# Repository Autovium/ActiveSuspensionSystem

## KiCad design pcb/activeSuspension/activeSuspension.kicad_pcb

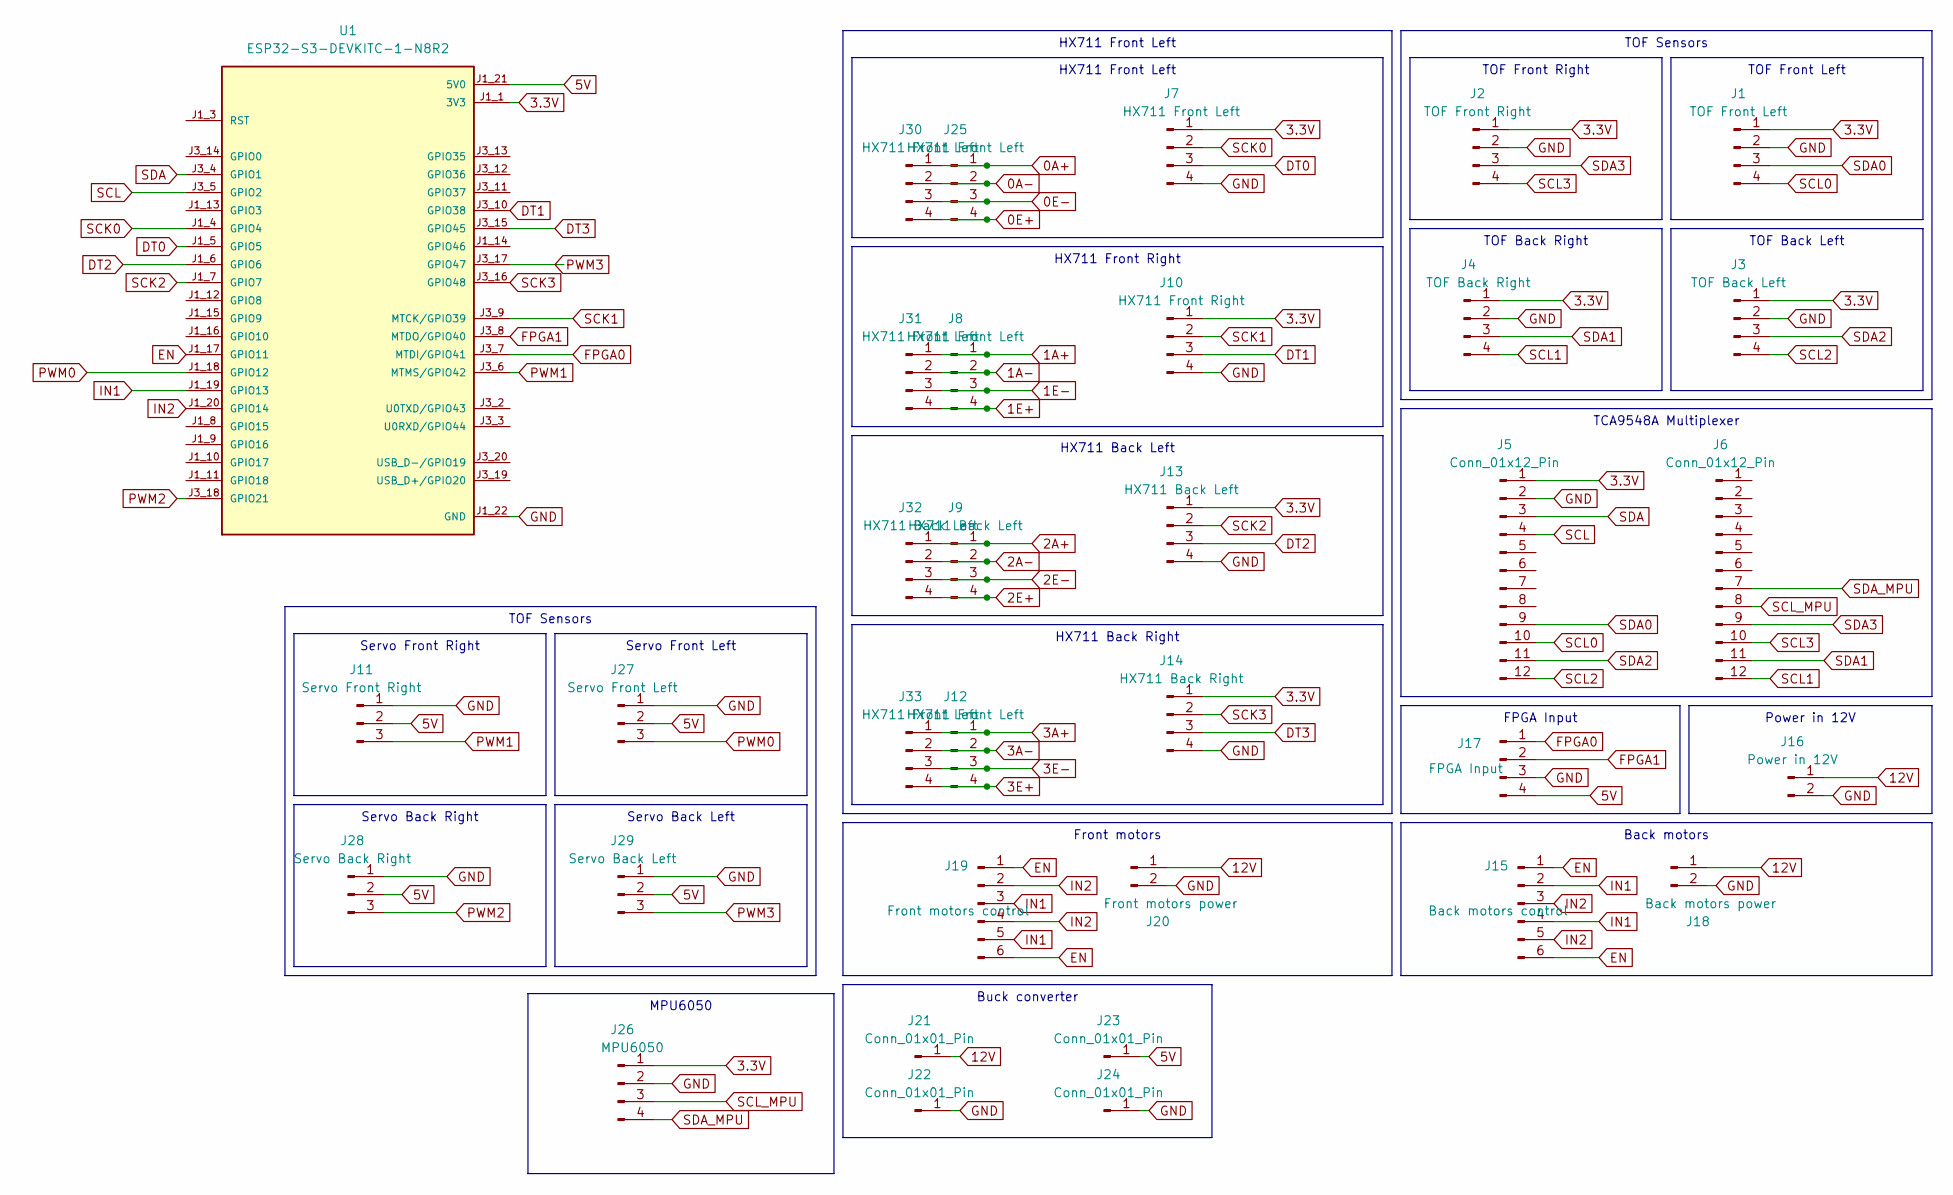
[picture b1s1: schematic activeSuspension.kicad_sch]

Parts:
J1: TOF Front Left; PinHeader_1x04_P2.54mm_Vertical
J2: TOF Front Right; PinHeader_1x04_P2.54mm_Vertical
J3: TOF Back Left; PinHeader_1x04_P2.54mm_Vertical
J4: TOF Back Right; PinHeader_1x04_P2.54mm_Vertical
J5, J6: Conn_01x12_Pin; PinHeader_1x12_P2.54mm_Vertical
J7, J8, J12, J25, J30, J31, J33: HX711 Front Left; PinHeader_1x04_P2.54mm_Vertical
J9, J13, J32: HX711 Back Left; PinHeader_1x04_P2.54mm_Vertical
J10: HX711 Front Right; PinHeader_1x04_P2.54mm_Vertical
J11: Servo Front Right; PinHeader_1x03_P2.54mm_Vertical
J14: HX711 Back Right; PinHeader_1x04_P2.54mm_Vertical
J15: Back motors control; PinHeader_1x06_P2.54mm_Vertical
J16: Power in 12V; PinHeader_1x02_P2.54mm_Vertical
J17: FPGA Input; PinHeader_1x04_P2.54mm_Vertical
J18: Back motors power; TerminalBlock_MetzConnect_Type101_RT01602HBWC_1x02_P5.08mm_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
J19: Front motors control; PinHeader_1x06_P2.54mm_Vertical
J20: Front motors power; TerminalBlock_MetzConnect_Type101_RT01602HBWC_1x02_P5.08mm_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
J21, J22, J23, J24: Conn_01x01_Pin; PinHeader_1x01_P2.54mm_Vertical
J26: MPU6050; PinHeader_1x04_P2.54mm_Vertical
J27: Servo Front Left; PinHeader_1x03_P2.54mm_Vertical
J28: Servo Back Right; PinHeader_1x03_P2.54mm_Vertical
J29: Servo Back Left; PinHeader_1x03_P2.54mm_Vertical
U1: ESP32-S3-DEVKITC-1-N8R2; XCVR_ESP32-S3-DEVKITC-1-N8R2; PARTREV V1

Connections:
0A+: J25.1, J30.1
0A-: J25.2, J30.2
0E+: J25.4, J30.4
0E-: J25.3, J30.3
1A+: J8.1, J31.1
1A-: J8.2, J31.2
1E+: J8.4, J31.4
1E-: J8.3, J31.3
2A+: J9.1, J32.1
2A-: J9.2, J32.2
2E+: J9.4, J32.4
2E-: J9.3, J32.3
3.3V: J1.1, J2.1, J3.1, J4.1, J5.1, J7.1, J10.1, J13.1, J14.1, J26.1, U1.J1_1 (3V3), U1.J1_2 (3V3)
3A+: J12.1, J33.1
3A-: J12.2, J33.2
3E+: J12.4, J33.4
3E-: J12.3, J33.3
5V: J11.2, J17.4, J23.1, J27.2, J28.2, J29.2, U1.J1_21 (5V0)
12V: J16.1, J18.1, J20.1, J21.1
DT0: J7.3, U1.J1_5 (GPIO5)
DT1: J10.3, U1.J3_10 (GPIO38)
DT2: J13.3, U1.J1_6 (GPIO6)
DT3: J14.3, U1.J3_13 (GPIO35), U1.J3_15 (GPIO45)
EN: J15.1, J15.6, J19.1, J19.6, U1.J1_17 (GPIO11)
FPGA0: J17.1, U1.J3_7 (MTDI/GPIO41)
FPGA1: J17.2, U1.J3_8 (MTDO/GPIO40)
GND: J1.2, J2.2, J3.2, J4.2, J5.2, J7.4, J10.4, J11.1, J13.4, J14.4, J16.2, J17.3, J18.2, J20.2, J22.1, J24.1, J26.2, J27.1, J28.1, J29.1, U1.J1_22 (GND), U1.J3_1 (GND), U1.J3_21 (GND), U1.J3_22 (GND)
IN1: J15.2, J15.4, J19.3, J19.5, U1.J1_19 (GPIO13)
IN2: J15.3, J15.5, J19.2, J19.4, U1.J1_20 (GPIO14)
PWM0: J27.3, U1.J1_18 (GPIO12)
PWM1: J11.3, U1.J3_6 (MTMS/GPIO42)
PWM2: J28.3, U1.J3_18 (GPIO21)
PWM3: J29.3, U1.J3_17 (GPIO47)
SCK0: J7.2, U1.J1_4 (GPIO4)
SCK1: J10.2, U1.J3_9 (MTCK/GPIO39)
SCK2: J13.2, U1.J1_7 (GPIO7)
SCK3: J14.2, U1.J3_12 (GPIO36), U1.J3_16 (GPIO48)
SCL: J5.4, U1.J3_5 (GPIO2)
SCL0: J1.4, J5.10
SCL1: J4.4, J6.12
SCL2: J3.4, J5.12
SCL3: J2.4, J6.10
SCL_MPU: J6.8, J26.3
SDA: J5.3, U1.J3_4 (GPIO1)
SDA0: J1.3, J5.9
SDA1: J4.3, J6.11
SDA2: J3.3, J5.11
SDA3: J2.3, J6.9
SDA_MPU: J6.7, J26.4

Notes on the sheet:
Back motors
FPGA Input
Buck converter
TOF Front Left
TOF Back Left
TOF Front Right
Servo Back Right
Front motors
HX711 Front Left
Servo Front Right
TOF Sensors
HX711 Back Right
MPU6050
Servo Front Left
HX711 Front Right
HX711 Back Left
Power in 12V
TOF Back Right
TCA9548A Multiplexer
Servo Back Left

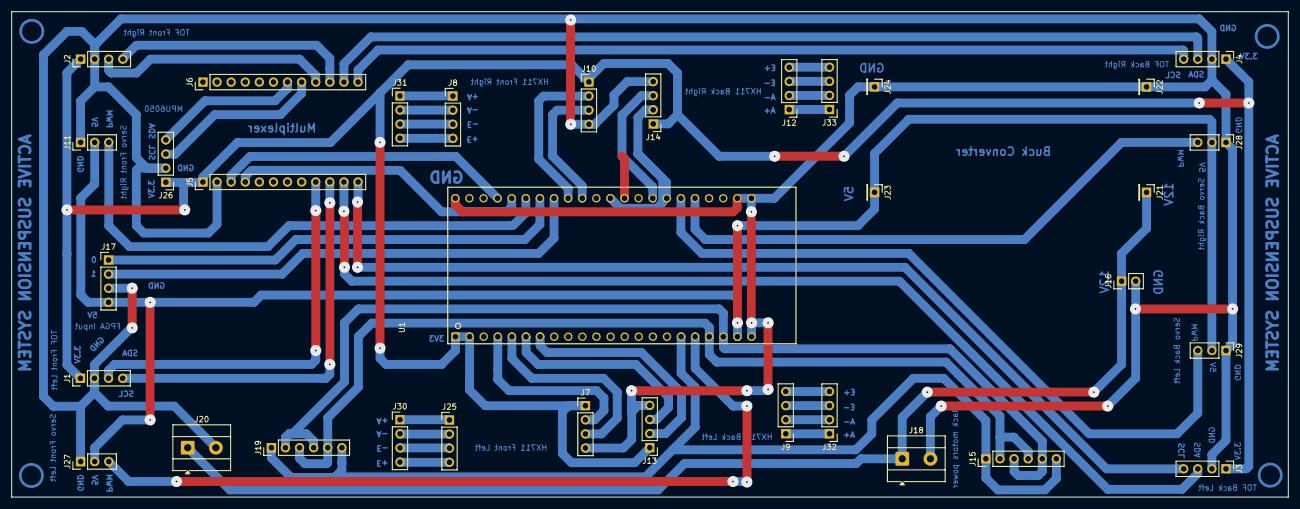
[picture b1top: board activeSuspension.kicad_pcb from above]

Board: 2 copper layers, 230.0 x 87.5 mm, 34 parts (0 on the bottom side), 49 nets.

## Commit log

2026-06-15 speed change added
2026-06-15 feedback corrected
2026-06-17 v2 created
2026-06-26 final
